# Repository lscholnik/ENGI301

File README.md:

# ENGI-301
Repository for ENGI301 course work

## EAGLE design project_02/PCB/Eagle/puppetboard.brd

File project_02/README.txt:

# PCB for mechanically actuated shadow puppets
See "docs" for a schematic pdf and mechanical diagram of the device.

See "PCB" for the schematic, board, and library Eagle files (in "Eagle") and the manufacturing files (in "MFG")

See my Hackster.io page for this project:
https://www.hackster.io/lms20/mechanically-actuated-shadow-puppets-using-pocketbeagle-145bd1

See additional information about code under "project_01" within this same repository

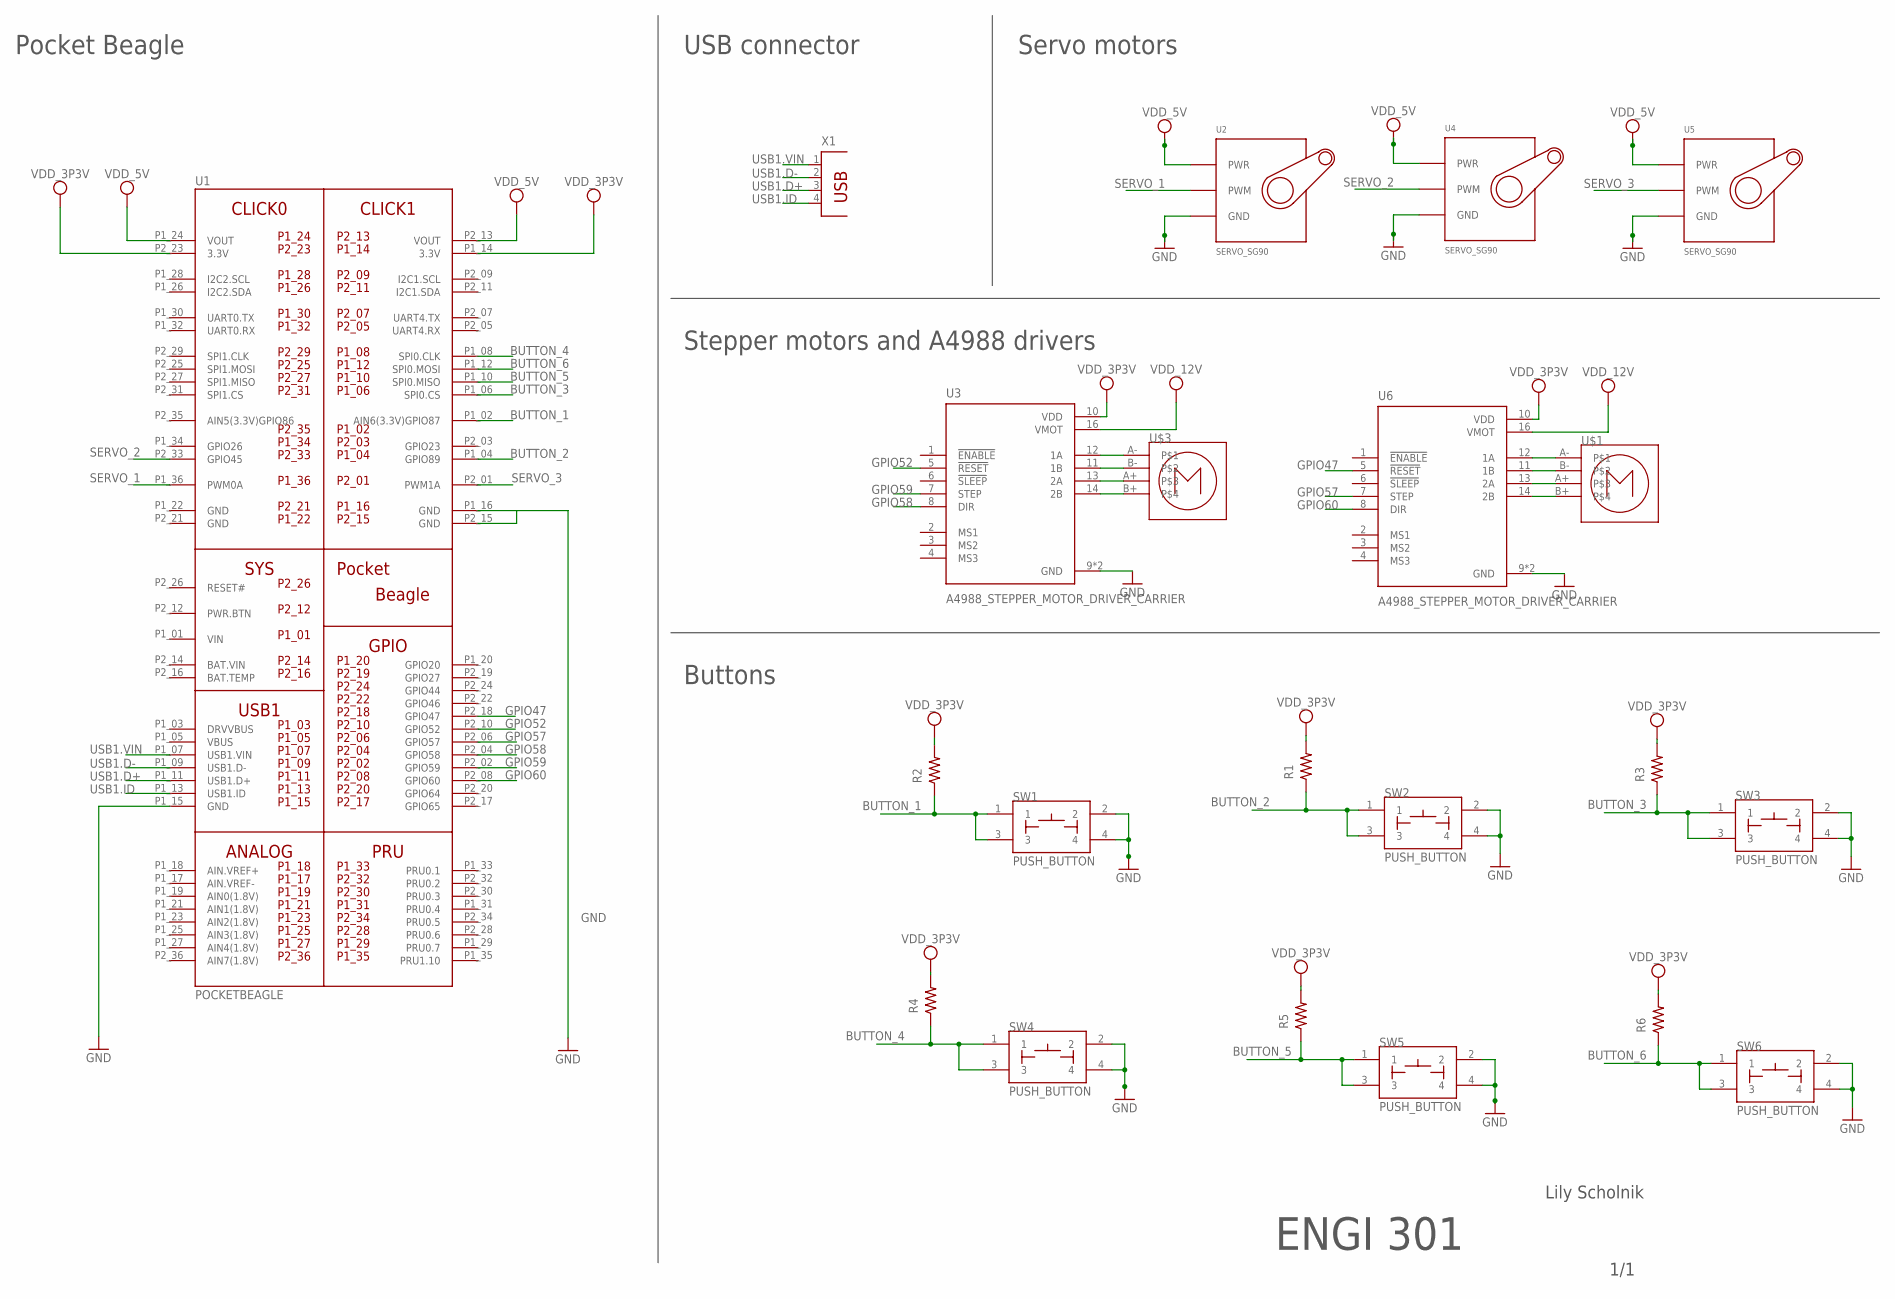
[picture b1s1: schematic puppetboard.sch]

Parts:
R1, R2, R3, R4, R5, R6: R_R0603; R0603
SW1, SW2, SW3, SW4, SW5, SW6: PUSH_BUTTON; BUTTON_12.5MM
U1: POCKETBEAGLE
U2, U4, U5: SERVO_SG90; SERVO-X1
U3, U6: A4988_STEPPER_MOTOR_DRIVER_CARRIER; MODULE_A4988_STEPPER_MOTOR_DRIVER_CARRIER
U$1, U$3: STEPPER_MOTOR
X1: PN61729

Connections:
BAT.VIN: U1.P2_14 (BAT.VIN)
BUTTON_1: R2.1, SW1.1, SW1.3, U1.P1_02 (AIN6(3.3V)GPIO87)
BUTTON_2: R1.1, SW2.1, SW2.3, U1.P1_04 (GPIO89)
BUTTON_3: R3.1, SW3.1, SW3.3, U1.P1_06 (SPI0.CS)
BUTTON_4: R4.1, SW4.1, SW4.3, U1.P1_08 (SPI0.CLK)
BUTTON_5: R5.1, SW5.1, SW5.3, U1.P1_10 (SPI0.MISO)
BUTTON_6: R6.1, SW6.1, SW6.3, U1.P1_12 (SPI0.MOSI)
GND: SW1.2, SW1.4, SW2.2, SW2.4, SW3.2, SW3.4, SW4.2, SW4.4, SW5.2, SW5.4, SW6.2, SW6.4, U1.P1_15 (GND), U1.P1_16 (GND), U1.P1_22 (GND), U1.P2_15 (GND), U1.P2_21 (GND), U2.GND, U3.9 (GND), U3.15 (GND), U4.GND, U5.GND, U6.9 (GND), U6.15 (GND)
GPIO47: U1.P2_18 (GPIO47), U6.5 (!RESET)
GPIO52: U1.P2_10 (GPIO52), U3.5 (!RESET)
GPIO57: U1.P2_06 (GPIO57), U6.7 (STEP)
GPIO58: U1.P2_04 (GPIO58), U3.8 (DIR)
GPIO59: U1.P2_02 (GPIO59), U3.7 (STEP)
GPIO60: U1.P2_08 (GPIO60), U6.8 (DIR)
unnamed: U6.12 (1A), U$1.A-
unnamed: U6.11 (1B), U$1.B-
unnamed: U6.13 (2A), U$1.A+
unnamed: U6.14 (2B), U$1.B+
unnamed: U3.12 (1A), U$3.A-
unnamed: U3.11 (1B), U$3.B-
unnamed: U3.13 (2A), U$3.A+
unnamed: U3.14 (2B), U$3.B+
SERVO_1: U1.P1_36 (PWM0A), U2.SIG (PWM)
SERVO_2: U1.P2_33 (GPIO45), U4.SIG (PWM)
SERVO_3: U1.P2_01 (PWM1A), U5.SIG (PWM)
USB1.D+: U1.P1_11 (USB1.D+), X1.3
USB1.D-: U1.P1_09 (USB1.D-), X1.2
USB1.ID: U1.P1_13 (USB1.ID), X1.4
USB1.VIN: U1.P1_07 (USB1.VIN), X1.1
VDD_3P3V: R1.2, R2.2, R3.2, R4.2, R5.2, R6.2, U1.P1_14 (3.3V), U1.P2_23 (3.3V), U3.10 (VDD), U6.10 (VDD)
VDD_5V: U1.P1_24 (VOUT), U1.P2_13 (VOUT), U2.PWR, U3.16 (VMOT), U4.PWR, U5.PWR, U6.16 (VMOT)
VIN: U1.P1_01 (VIN)

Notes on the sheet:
1/1
Lily Scholnik
ENGI 301
Buttons
Stepper motors and A4988 drivers
USB connector
Servo motors
Pocket Beagle

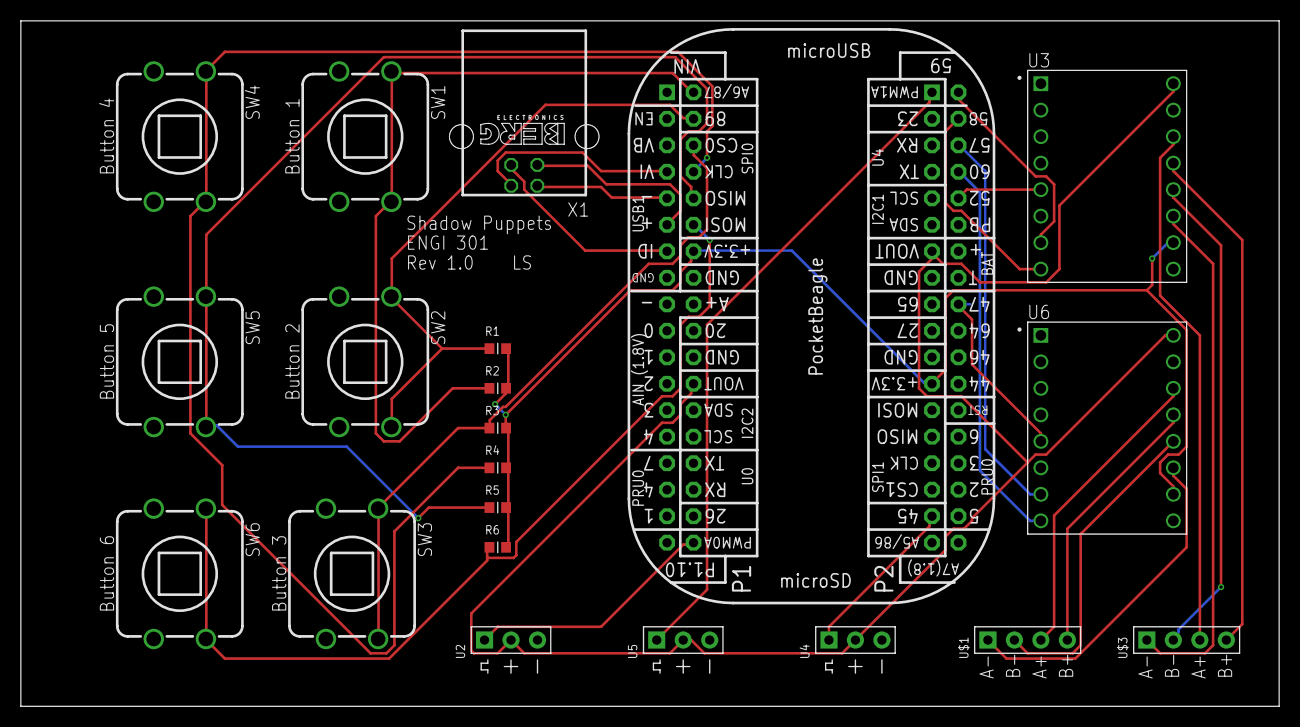
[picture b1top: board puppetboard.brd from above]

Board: 4 copper layers, 120.6 x 65.7 mm, 21 parts (0 on the bottom side), 30 nets.

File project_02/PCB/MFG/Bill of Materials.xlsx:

Designator | Value | Footprint | Populate | MPN | Manufacturer
R1 |  | R0603 | 1 | MF-RES-0805-1K | MacroFab
R2 |  | R0603 | 1 | MF-RES-0805-1K | MacroFab
R3 |  | R0603 | 1 | MF-RES-0805-1K | MacroFab
R4 |  | R0603 | 1 | MF-RES-0805-1K | MacroFab
R5 |  | R0603 | 1 | MF-RES-0805-1K | MacroFab
R6 |  | R0603 | 1 | MF-RES-0805-1K | MacroFab
SW1 | PUSH_BUTTON | BUTTON_12.5MM | 0 | BIG PUSHBUTTON POWER SWITCH HP | Pololu
SW2 | PUSH_BUTTON | BUTTON_12.5MM | 0 | BIG PUSHBUTTON POWER SWITCH HP | Pololu
SW3 | PUSH_BUTTON | BUTTON_12.5MM | 0 | BIG PUSHBUTTON POWER SWITCH HP | Pololu
SW4 | PUSH_BUTTON | BUTTON_12.5MM | 0 | BIG PUSHBUTTON POWER SWITCH HP | Pololu
SW5 | PUSH_BUTTON | BUTTON_12.5MM | 0 | BIG PUSHBUTTON POWER SWITCH HP | Pololu
SW6 | PUSH_BUTTON | BUTTON_12.5MM | 0 | BIG PUSHBUTTON POWER SWITCH HP | Pololu
U1 | POCKETBEAGLE | POCKETBEAGLE | 0 | POCKETBEAGLE | BeagleBoard
U2 | SERVO_SG90 | SERVO-X1 | 0 | 154 | Adafruit Industries
U3 | A4988_STEPPER_MOTOR_DRIVER_CARRIER | MODULE_A4988_STEPPER_MOTOR_DRIVER_CARRIER | 0 | A4988 STEPPER MOTOR DRIVER CARRIER | Pololu
U4 | SERVO_SG90 | SERVO-X1 | 0 | 154 | Adafruit Industries
U5 | SERVO_SG90 | SERVO-X1 | 0 | 154 | Adafruit Industries
U6 | A4988_STEPPER_MOTOR_DRIVER_CARRIER | MODULE_A4988_STEPPER_MOTOR_DRIVER_CARRIER | 0 | A4988 STEPPER MOTOR DRIVER CARRIER | Pololu
X1 |  | PN61729 | 0 | 87583-2010BLF | Amphenol Communications Solutions

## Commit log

2023-04-03 fixing of engi repository
2023-04-04 Fixing folder organization
2023-04-04 Updating readme file
2023-05-03 project 2 files
2023-05-03 project 2 uploads
2023-05-03 board screengrabs
2024-09-10 Update people_counter.py TEST EDIT
    TEST EDIT
2024-09-10 People_counter.py TEST dev
